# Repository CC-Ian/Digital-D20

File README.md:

# Big Electronic D20

This project began several years ago, before pixel dice became widely available. Inspired by existing designs but aiming for something unique, this marks my first foray into PCB art. By adding artwork to the solder mask layer, the FR4 substrate is exposed, allowing light to shine through. Combined with a 3D-printed frame, a mainboard featuring LEDs, and an IMU, the result is a visually striking D20 that comes to life when rolled.

## Showcase

## Faces

- Each face is an equilateral triangle, 1.5" per edge.
- Single-sided PCBs with gold-plated numbers.
- Solder mask is relieved around each number for clear illumination.
- Lightning patterns are masked out for added visual interest.
- Designs were refined following prototype testing with various patterns.

## Frame

- Constructed from MJF-printed nylon in an icosahedral shape.
- Features inset shelves for gluing PCB faces.
- Includes cut-outs along two opposing spokes to accommodate the rectangular mainboard.

## Mainboard

- STM32L412KB microcontroller.
- LIS2DW12 MEMS IMU.
- 32 addressable LEDs.
- Voltage regulators and LiPo battery charging circuitry.
- Ultra-low power design: enters deep sleep mode when not in use.

### Operation

- The IMU detects motion, waking the microcontroller.
- LEDs activate and display a lightning animation while the die is in motion.
- The IMU is regularly polled during animation.
- When the die comes to rest, a final measurement determines the top face using cosine similarity.
- The face value determines the display color: pure red for 1, pure green for 20, with a linear gradient for intermediate values.
- The color is shown for a few seconds before returning to sleep mode.

### Power Consumption

- At rest: ~5μA, yielding a theoretical shelf life of ~5 years with a 400mAh battery.
- During operation: ~50mA, for a theoretical runtime of ~10 hours.
- Designed for intermittent use, suitable for multiple gaming sessions per charge.

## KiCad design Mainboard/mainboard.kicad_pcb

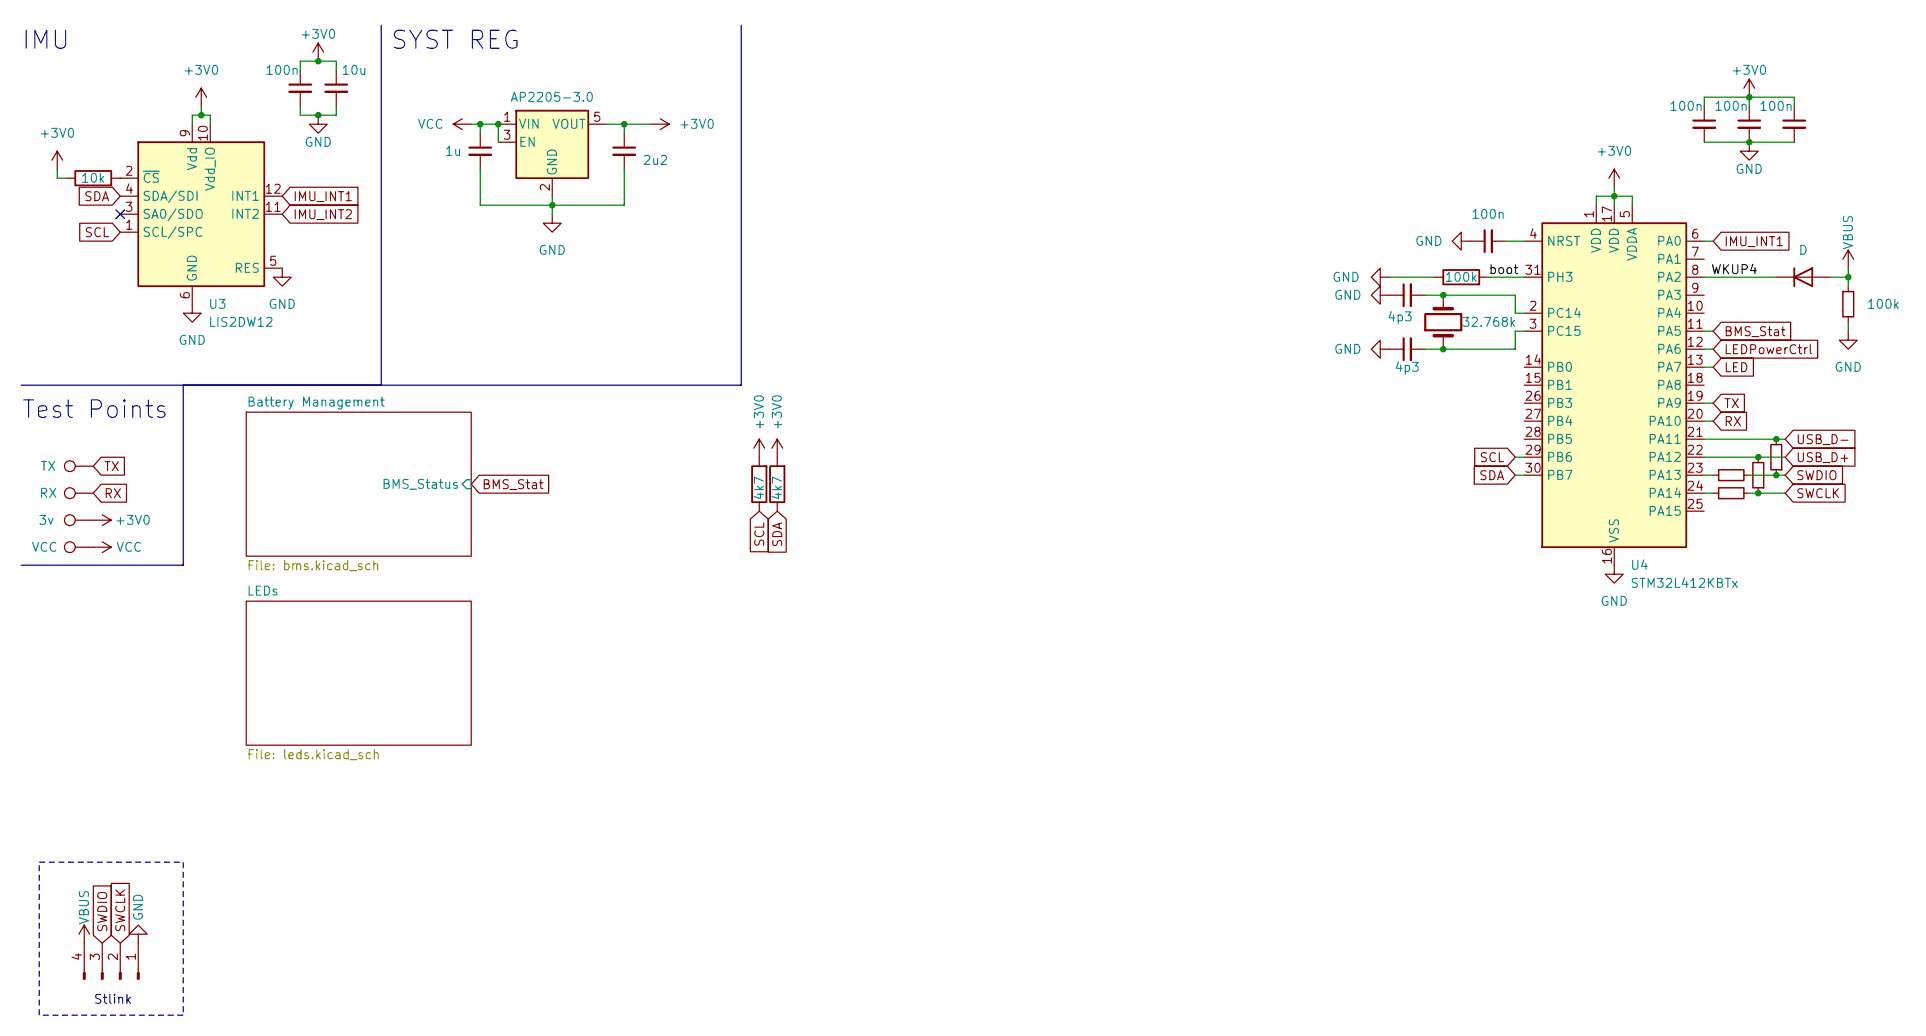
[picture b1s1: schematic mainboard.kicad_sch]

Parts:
3v0: 3v; TestPoint_Pad_D1.0mm
C3, C5, C6, C7, C10: 100n; C_0402_1005Metric
C4: 10u; C_0402_1005Metric
C8: 1u; C_0402_1005Metric
C9: 2u2; C_0402_1005Metric
C12, C13: 4p3; C_0402_1005Metric
D33: D; D_SOD-323
J1: Conn_01x04_Pin; PinHeader_1x04_P2.54mm_Vertical
R2: 10k; R_0402_1005Metric
R3, R12: R_Small; R_0201_0603Metric
R4, R10: 100k; R_0402_1005Metric
R6, R7: 4k7; R_0402_1005Metric
R13, R14: R_Small; R_0402_1005Metric
RX1: RX; TestPoint_Pad_D1.0mm
TP9: VCC; TestPoint_Pad_D1.0mm
TX1: TX; TestPoint_Pad_D1.0mm
U1: AP2205-3.0; SOT-23-5
U3: LIS2DW12; LGA-12_2x2mm_P0.5mm
U4: STM32L412KBTx; LQFP-32_7x7mm_P0.8mm
Y1: 32.768k; Crystal_SMD_3215-2Pin_3.2x1.5mm

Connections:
+3V0: 3v0.1, C3.1, C4.1, C5.1, C6.1, C7.1, C9.1, R2.1, R6.2, R7.2, U1.5 (VOUT), U3.9 (Vdd), U3.10 (Vdd_IO), U4.1 (VDD), U4.5 (VDDA), U4.17 (VDD)
/WKUP4: D33.1 (K), U4.8 (PA2)
/boot: R4.2, U4.31 (PH3)
BMS_Stat: U4.11 (PA5); also elsewhere on the board
GND: C3.2, C4.2, C5.2, C6.2, C7.2, C8.2, C9.2, C10.1, C12.1, C13.1, J1.1, R4.1, R10.2, U1.2 (GND), U3.5 (RES), U3.6 (GND), U3.7 (GND), U3.8 (GND), U4.16 (VSS), U4.32 (VSS); also elsewhere on the board
IMU_INT1: U3.12 (INT1), U4.6 (PA0)
IMU_INT2: U3.11 (INT2)
LED: U4.13 (PA7); also elsewhere on the board
LEDPowerCtrl: U4.12 (PA6); also elsewhere on the board
unnamed: R2.2, U3.2 (~CS)
unnamed: C10.2, U4.4 (NRST)
unnamed: R3.1, U4.23 (PA13)
unnamed: R12.1, U4.24 (PA14)
unnamed: C12.2, U4.2 (PC14), Y1.2
unnamed: C13.2, U4.3 (PC15), Y1.1
RX: RX1.1, U4.20 (PA10)
SCL: R6.1, U3.1 (SCL/SPC), U4.29 (PB6)
SDA: R7.1, U3.4 (SDA/SDI), U4.30 (PB7)
SWCLK: J1.2, R12.2, R13.1
SWDIO: J1.3, R3.2, R14.1
TX: TX1.1, U4.19 (PA9)
USB_D+: R13.2, U4.22 (PA12)
USB_D-: R14.2, U4.21 (PA11)
VBUS: D33.2 (A), J1.4, R10.1; also elsewhere on the board
VCC: C8.1, TP9.1, U1.1 (VIN), U1.3 (EN); also elsewhere on the board

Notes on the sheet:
Test Points
SYST REG
Stlink
IMU

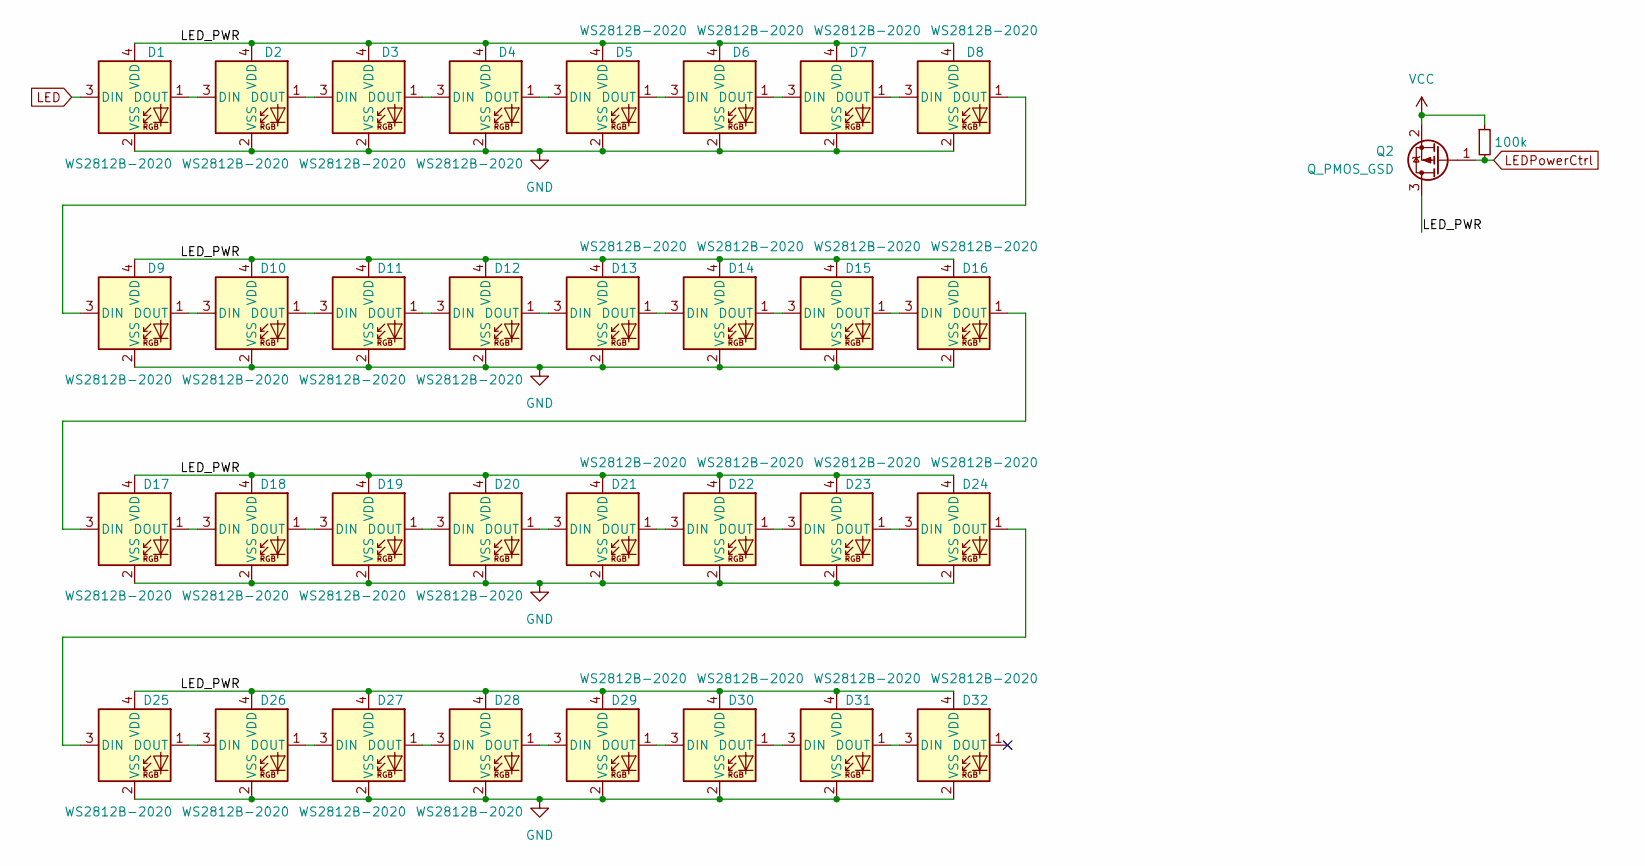
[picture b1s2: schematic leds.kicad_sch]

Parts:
D1, D2, D3, D4, D5, D6, D7, D8, D9, D10, D11, D12, D13, D14, D15, D16, D17, D18, D19, D20, D21, D22, D23, D24, D25, D26, D27, D28, D29, D30, D31, D32: WS2812B-2020; LED_WS2812B-2020_PLCC4_2.0x2.0mm
Q2: Q_PMOS_GSD; SOT-23
R9: 100k; R_0402_1005Metric

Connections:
/LEDs/LED_PWR: D1.4 (VDD), D2.4 (VDD), D3.4 (VDD), D4.4 (VDD), D5.4 (VDD), D6.4 (VDD), D7.4 (VDD), D8.4 (VDD), D9.4 (VDD), D10.4 (VDD), D11.4 (VDD), D12.4 (VDD), D13.4 (VDD), D14.4 (VDD), D15.4 (VDD), D16.4 (VDD), D17.4 (VDD), D18.4 (VDD), D19.4 (VDD), D20.4 (VDD), D21.4 (VDD), D22.4 (VDD), D23.4 (VDD), D24.4 (VDD), D25.4 (VDD), D26.4 (VDD), D27.4 (VDD), D28.4 (VDD), D29.4 (VDD), D30.4 (VDD), D31.4 (VDD), D32.4 (VDD), Q2.3 (D)
GND: D1.2 (VSS), D2.2 (VSS), D3.2 (VSS), D4.2 (VSS), D5.2 (VSS), D6.2 (VSS), D7.2 (VSS), D8.2 (VSS), D9.2 (VSS), D10.2 (VSS), D11.2 (VSS), D12.2 (VSS), D13.2 (VSS), D14.2 (VSS), D15.2 (VSS), D16.2 (VSS), D17.2 (VSS), D18.2 (VSS), D19.2 (VSS), D20.2 (VSS), D21.2 (VSS), D22.2 (VSS), D23.2 (VSS), D24.2 (VSS), D25.2 (VSS), D26.2 (VSS), D27.2 (VSS), D28.2 (VSS), D29.2 (VSS), D30.2 (VSS), D31.2 (VSS), D32.2 (VSS); also elsewhere on the board
LED: D1.3 (DIN); also elsewhere on the board
LEDPowerCtrl: Q2.1 (G), R9.2; also elsewhere on the board
unnamed: D1.1 (DOUT), D2.3 (DIN)
unnamed: D2.1 (DOUT), D3.3 (DIN)
unnamed: D3.1 (DOUT), D4.3 (DIN)
unnamed: D4.1 (DOUT), D5.3 (DIN)
unnamed: D5.1 (DOUT), D6.3 (DIN)
unnamed: D6.1 (DOUT), D7.3 (DIN)
unnamed: D7.1 (DOUT), D8.3 (DIN)
unnamed: D8.1 (DOUT), D9.3 (DIN)
unnamed: D9.1 (DOUT), D10.3 (DIN)
unnamed: D10.1 (DOUT), D11.3 (DIN)
unnamed: D11.1 (DOUT), D12.3 (DIN)
unnamed: D12.1 (DOUT), D13.3 (DIN)
unnamed: D13.1 (DOUT), D14.3 (DIN)
unnamed: D14.1 (DOUT), D15.3 (DIN)
unnamed: D15.1 (DOUT), D16.3 (DIN)
unnamed: D16.1 (DOUT), D17.3 (DIN)
unnamed: D17.1 (DOUT), D18.3 (DIN)
unnamed: D18.1 (DOUT), D19.3 (DIN)
unnamed: D19.1 (DOUT), D20.3 (DIN)
unnamed: D20.1 (DOUT), D21.3 (DIN)
unnamed: D21.1 (DOUT), D22.3 (DIN)
unnamed: D22.1 (DOUT), D23.3 (DIN)
unnamed: D23.1 (DOUT), D24.3 (DIN)
unnamed: D24.1 (DOUT), D25.3 (DIN)
unnamed: D25.1 (DOUT), D26.3 (DIN)
unnamed: D26.1 (DOUT), D27.3 (DIN)
unnamed: D27.1 (DOUT), D28.3 (DIN)
unnamed: D28.1 (DOUT), D29.3 (DIN)
unnamed: D29.1 (DOUT), D30.3 (DIN)
unnamed: D30.1 (DOUT), D31.3 (DIN)
unnamed: D31.1 (DOUT), D32.3 (DIN)
VCC: Q2.2 (S), R9.1; also elsewhere on the board

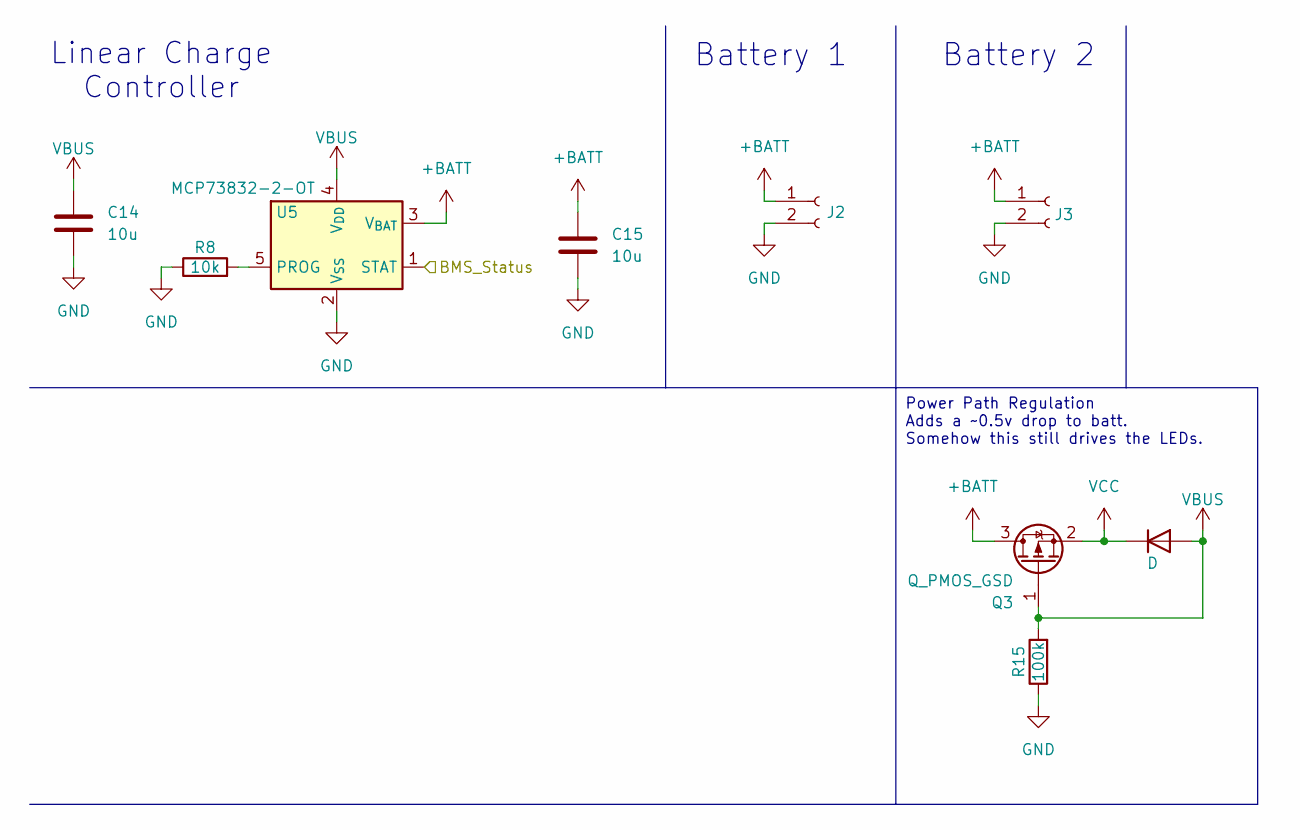
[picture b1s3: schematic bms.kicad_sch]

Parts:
C14, C15: 10u; C_0603_1608Metric
D34: D; D_SOD-323
J2, J3: Conn_01x02_Socket; PinHeader_1x02_P2.00mm_Vertical
Q3: Q_PMOS_GSD; SOT-23
R8: 10k; R_0402_1005Metric
R15: 100k; R_0402_1005Metric
U5: MCP73832-2-OT; SOT-23-5

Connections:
+BATT: C15.1, J2.1, J3.1, Q3.3 (D), U5.3 (V_{BAT})
BMS_Stat: U5.1 (STAT); also elsewhere on the board
GND: C14.2, C15.2, J2.2, J3.2, R8.1, R15.1, U5.2 (V_{SS}); also elsewhere on the board
unnamed: R8.2, U5.5 (PROG)
VBUS: C14.1, D34.2 (A), Q3.1 (G), R15.2, U5.4 (V_{DD}); also elsewhere on the board
VCC: D34.1 (K), Q3.2 (S); also elsewhere on the board

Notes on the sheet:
Battery 1
Battery 2
Linear Charge Controller
Power Path Regulation Adds a ~0.5v drop to batt. Somehow this still drives the LEDs.

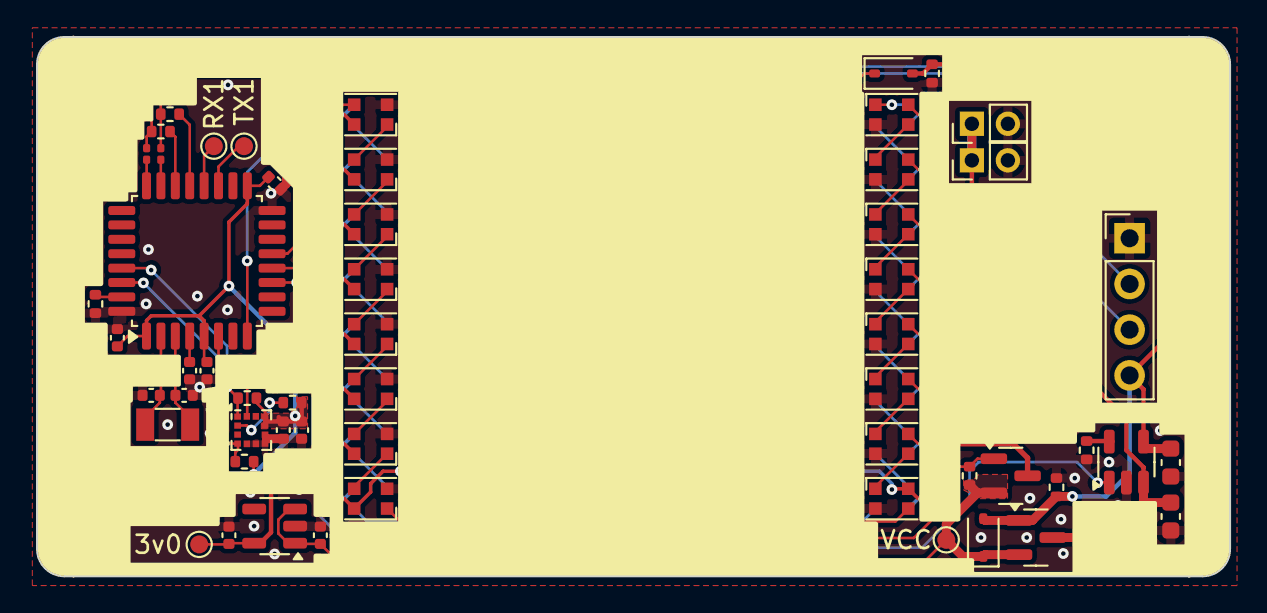
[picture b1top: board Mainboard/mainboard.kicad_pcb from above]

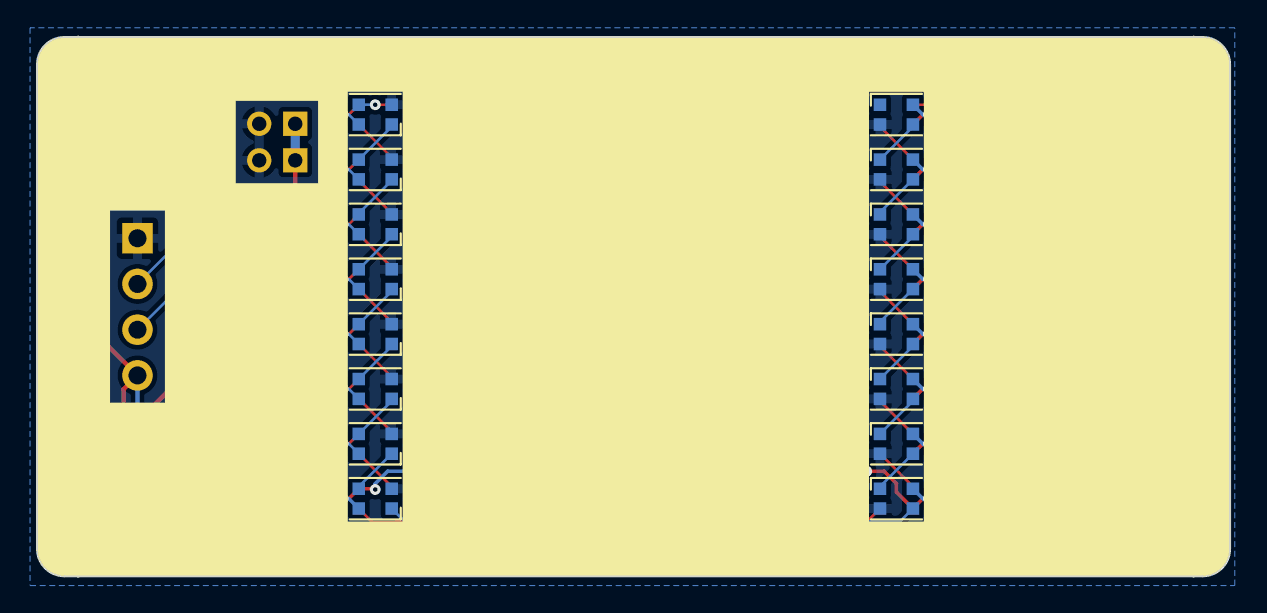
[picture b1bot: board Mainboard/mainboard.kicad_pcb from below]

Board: 2 copper layers, 66.3 x 30.0 mm, 72 parts (16 on the bottom side), 58 nets.

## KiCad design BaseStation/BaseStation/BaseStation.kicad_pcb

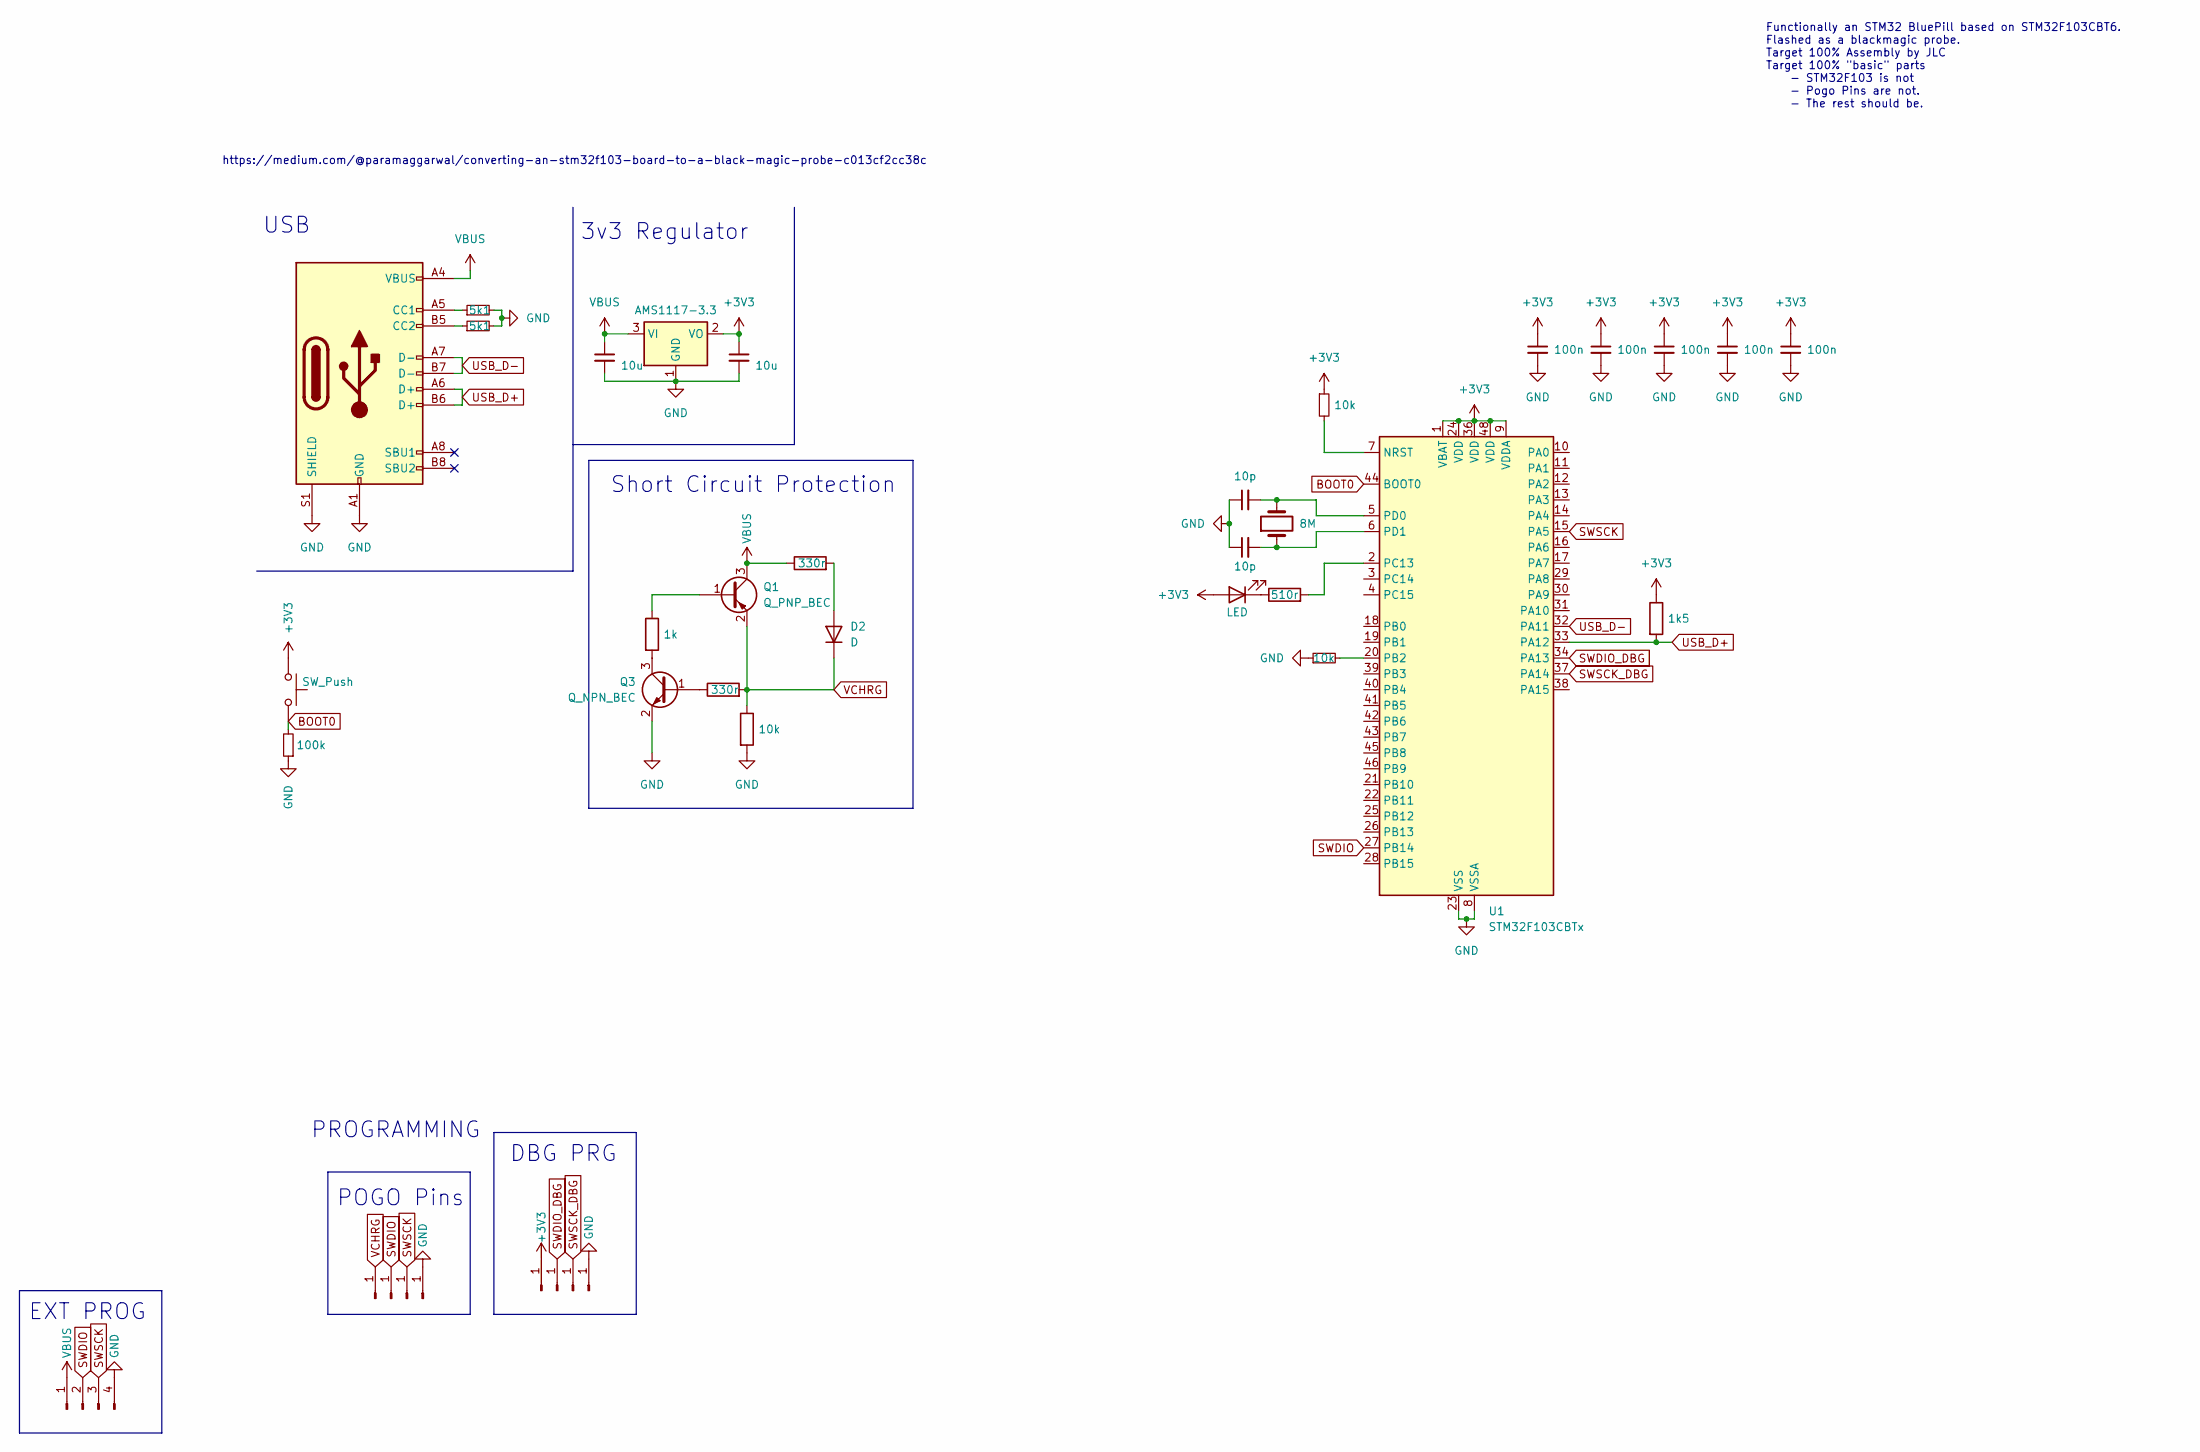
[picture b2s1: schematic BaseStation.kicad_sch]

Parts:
C1, C2: 10u; C_0603_1608Metric
C3, C4: 10p; C_0402_1005Metric
C5, C6, C7, C8, C9: 100n; C_0402_1005Metric
D1: LED; LED_0603_1608Metric
D2: D; D_SOD-323
J1: USB_C_Receptacle_USB2.0_16P; USB_C_Receptacle_HRO_TYPE-C-31-M-12
J2, J3, J4, J5: Conn_01x01_Pin; TestPoint_Loop_D3.50mm_Drill0.9mm_Beaded
J6, J7, J8, J9: Conn_01x01_Pin; TestPoint_Pad_D1.5mm
J10: Conn_01x04_Pin; PinHeader_1x04_P2.54mm_Horizontal
Q1: Q_PNP_BEC; SOT-23
Q3: Q_NPN_BEC; SOT-23
R1, R2: 5k1; R_0603_1608Metric
R3, R4: 10k; R_0603_1608Metric
R5: 100k; R_0603_1608Metric
R6: 510r; R_0603_1608Metric
R7: 1k; R_0402_1005Metric
R8, R10: 330r; R_0402_1005Metric
R9: 10k; R_0402_1005Metric
R11: 1k5; R_0402_1005Metric
SW1: SW_Push; SW_SPST_SKQG_WithStem
U1: STM32F103CBTx; LQFP-48_7x7mm_P0.5mm
U2: AMS1117-3.3; SOT-223-3_TabPin2
Y2: 8M; Crystal_SMD_5032-2Pin_5.0x3.2mm; Part X50328MSB2GI

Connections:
+3V3: C2.1, C5.1, C6.1, C7.1, C8.1, C9.1, D1.2 (A), J6.1, R3.1, R11.1, SW1.1, U1.1 (VBAT), U1.9 (VDDA), U1.24 (VDD), U1.36 (VDD), U1.48 (VDD), U2.2 (VO)
BOOT0: R5.2, SW1.2, U1.44 (BOOT0)
GND: C1.2, C2.2, C3.1, C4.1, C5.2, C6.2, C7.2, C8.2, C9.2, J1.A1 (GND), J1.A12 (GND), J1.B1 (GND), J1.B12 (GND), J1.S1 (SHIELD), J5.1, J9.1, J10.4, Q3.2 (E), R1.2, R2.2, R4.1, R5.1, R9.2, U1.8 (VSSA), U1.23 (VSS), U1.35 (VSS), U1.47 (VSS), U2.1 (GND)
unnamed: D1.1 (K), R6.1
unnamed: D2.2 (A), R10.2
unnamed: J1.A5 (CC1), R1.1
unnamed: J1.B5 (CC2), R2.1
unnamed: Q1.1 (B), R7.1
unnamed: Q3.1 (B), R8.1
unnamed: Q3.3 (C), R7.2
unnamed: R3.2, U1.7 (NRST)
unnamed: R4.2, U1.20 (PB2)
unnamed: R6.2, U1.2 (PC13)
unnamed: C3.2, U1.5 (PD0), Y2.2
unnamed: C4.2, U1.6 (PD1), Y2.1
SWDIO: J3.1, J10.2, U1.27 (PB14), U1.28 (PB15)
SWDIO_DBG: J7.1, U1.34 (PA13)
SWSCK: J4.1, J10.3, U1.15 (PA5)
SWSCK_DBG: J8.1, U1.37 (PA14)
USB_D+: J1.A6 (D+), J1.B6 (D+), R11.2, U1.33 (PA12)
USB_D-: J1.A7 (D-), J1.B7 (D-), U1.32 (PA11)
VBUS: C1.1, J1.A4 (VBUS), J1.A9 (VBUS), J1.B4 (VBUS), J1.B9 (VBUS), J10.1, Q1.3 (C), R10.1, U2.3 (VI)
VCHRG: D2.1 (K), J2.1, Q1.2 (E), R8.2, R9.1

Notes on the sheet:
DBG PRG
3v3 Regulator
Short Circuit Protection
USB
https://medium.com/@paramaggarwal/converting-an-stm32f103-board-to-a-black-magic-probe-c013cf2cc38c
PROGRAMMING
EXT PROG
Functionally an STM32 BluePill based on STM32F103CBT6. Flashed as a blackmagic probe. Target 100% Assembly by JLC Target 100% "basic" parts - STM32F103 is not - Pogo Pins are not. - The rest should be.
POGO Pins

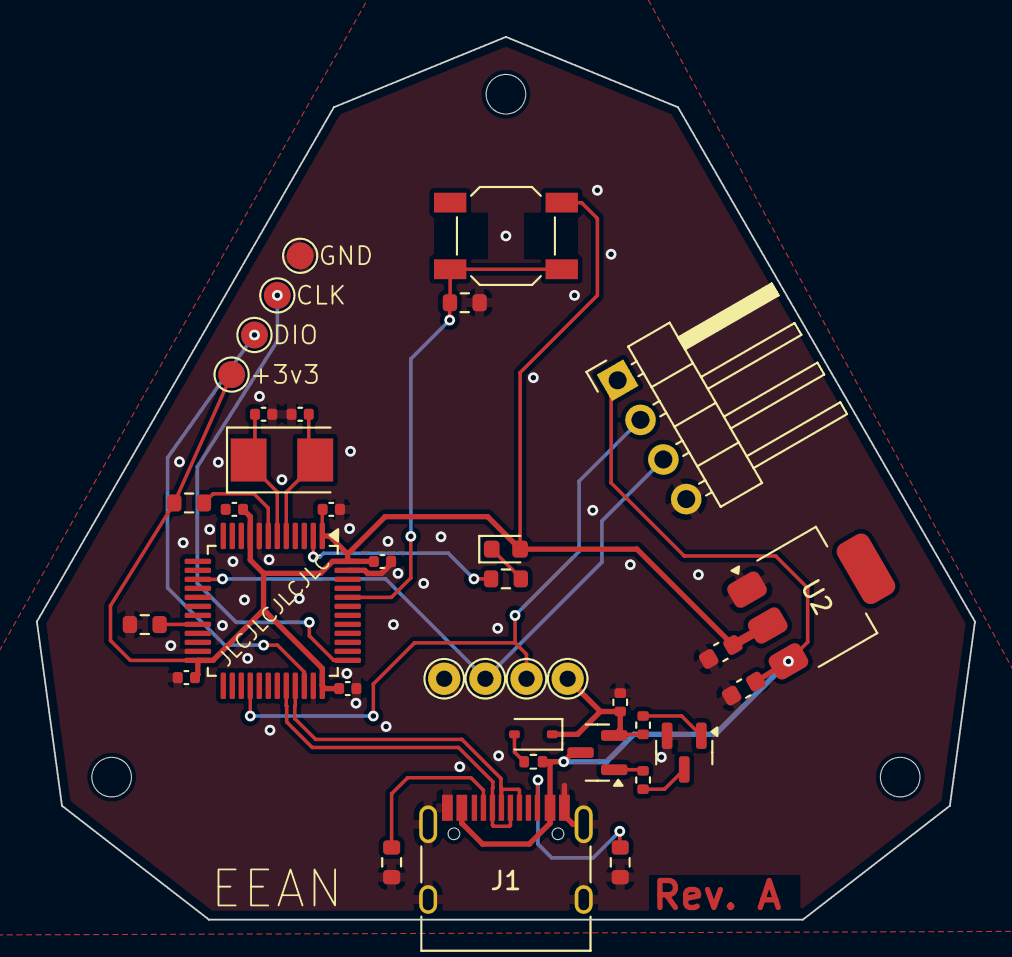
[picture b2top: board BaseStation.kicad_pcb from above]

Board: 2 copper layers, 52.1 x 49.0 mm, 37 parts (0 on the bottom side), 23 nets.

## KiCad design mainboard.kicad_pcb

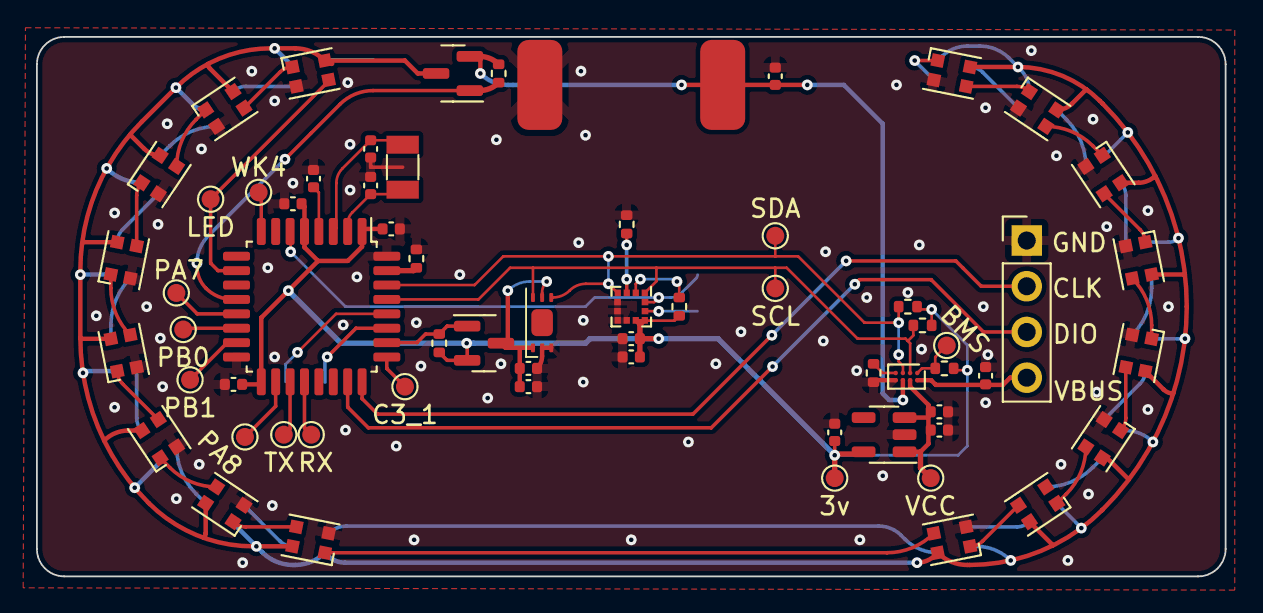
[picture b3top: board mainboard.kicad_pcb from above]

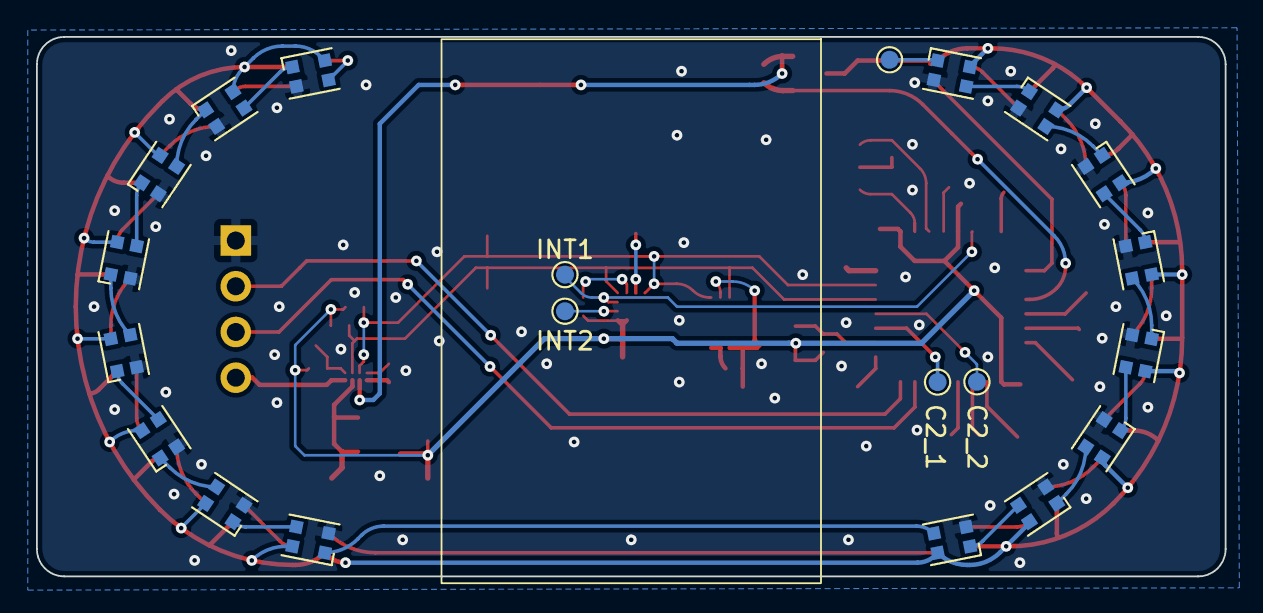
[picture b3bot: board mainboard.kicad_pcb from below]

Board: 2 copper layers, 66.0 x 30.0 mm, 52 parts (4 on the bottom side), 33 nets.

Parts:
BT1: 200mAh; battery_20x30
C1, C4: 10u; C_0402_1005Metric
C2, C8, C11: 1u; C_0402_1005Metric
C3, C5, C6, C7, C10, C14, C15: 100n; C_0402_1005Metric
C9: 2u2; C_0402_1005Metric
C12, C13: 4p3; C_0402_1005Metric
J1: Conn_01x04_Pin; PinHeader_1x04_P2.54mm_Vertical
Q1, Q2: Q_PMOS_GSD; SOT-23
R1, R2, R4, R5: 10k; R_0402_1005Metric
R3: 0; R_0402_1005Metric
R6, R7: 4k7; R_0402_1005Metric
R8, R9: 100k; R_0402_1005Metric
RX1: RX; TestPoint_Pad_D1.0mm
TP1: PB0; TestPoint_Pad_D1.0mm
TP2: PA7; TestPoint_Pad_D1.0mm
TP3: PB1; TestPoint_Pad_D1.0mm
TP4: PA8; TestPoint_Pad_D1.0mm
TP5: SDA; TestPoint_Pad_D1.0mm
TP6: SCL; TestPoint_Pad_D1.0mm
TP7: INT1; TestPoint_Pad_D1.0mm
TP8: INT2; TestPoint_Pad_D1.0mm
TP9: VCC; TestPoint_Pad_D1.0mm
TP10: 3v; TestPoint_Pad_D1.0mm
TP11: BMS; TestPoint_Pad_D1.0mm
TP12: LED; TestPoint_Pad_D1.0mm
TP13: WK4; TestPoint_Pad_D1.0mm
TP14: C2_1; TestPoint_Pad_D1.0mm
TP15: C2_2; TestPoint_Pad_D1.0mm
TP16: C3_1; TestPoint_Pad_D1.0mm
TP17: TX; TestPoint_Pad_D1.0mm
U1: AP2205-3.0; SOT-23-5
U2: BQ21080; Texas_DSBGA-8-1.04x1.59mm
U3: LIS2DW12; LGA-12_2x2mm_P0.5mm
U4: STM32L412KBTx; LQFP-32_7x7mm_P0.8mm
U5: BH1730; WSOF6
Y1: 32.768k; Crystal_SMD_3215-2Pin_3.2x1.5mm

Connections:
+3V0: C3.1, C4.1, C5.1, C6.1, C7.1, C9.1, Q1.2 (S), R1.2, R2.1, R6.2, R7.2, R8.1, TP10.1, U1.5 (VOUT), U3.9 (Vdd), U3.10 (Vdd_IO), U4.1 (VDD), U4.5 (VDDA), U4.17 (VDD)
+BATT: BT1.1 (+), C11.1, Q2.2 (S), R9.1, U2.C2 (BAT)
ALVCC: C14.1, C15.1, Q1.3 (D), U5.1 (VCC), U5.5 (DVI)
BH1730PowerCtrl: Q1.1 (G), R8.2, U4.26 (PB3)
GND: BT1.2 (-), C1.2, C2.2, C3.2, C4.2, C5.2, C6.2, C7.2, C8.2, C9.2, C10.1, C11.2, C12.1, C13.1, C14.2, C15.2, J1.1, R3.1, R4.1, R5.1, U1.2 (GND), U2.D2 (GND), U3.5 (RES), U3.6 (GND), U3.7 (GND), U3.8 (GND), U4.16 (VSS), U4.32 (VSS), U5.2 (INT), U5.3 (GND)
IMU_INT1: TP7.1, U3.12 (INT1), U4.6 (PA0)
IMU_INT2: TP8.1, U3.11 (INT2)
LED IN: TP12.1, U4.10 (PA4)
LEDPowerCtrl: Q2.1 (G), R9.2, U4.12 (PA6)
unnamed: R3.2, U3.3 (SA0/SDO)
unnamed: R2.2, U3.2 (~CS)
unnamed: C10.2, U4.4 (NRST)
unnamed: TP2.1, U4.13 (PA7)
unnamed: TP4.1, U4.18 (PA8)
unnamed: TP1.1, U4.14 (PB0)
unnamed: TP3.1, U4.15 (PB1)
unnamed: C12.2, U4.2 (PC14), Y1.2
unnamed: C13.2, U4.3 (PC15), Y1.1
unnamed: R4.2, U4.31 (PH3)
RX: RX1.1, U4.20 (PA10)
SCL: R6.1, TP6.1, U2.B1 (SCL), U3.1 (SCL/SPC), U4.29 (PB6), U5.6 (SCL)
SDA: R7.1, TP5.1, U2.C1 (SDA), U3.4 (SDA/SDI), U4.30 (PB7), U5.4 (SDA)
SWCLK: J1.2, U4.24 (PA14)
SWDIO: J1.3, U4.23 (PA13)
TSC_G2_IO1: TP14.1, U4.27 (PB4)
TSC_G2_IO2: TP15.1, U4.28 (PB5)
TSC_G3_IO1: TP16.1, U4.25 (PA15)
TS|MR: R5.2, U2.D1 (TS|MR)
TX: TP17.1, U4.19 (PA9)
VBUS: C2.1, J1.4, U2.A2 (IN)
VCC: C1.1, C8.1, TP9.1, U1.1 (VIN), U1.3 (EN), U2.B2 (SYS)
WKUP4: TP13.1, U4.8 (PA2)
~BMS_INT: R1.1, TP11.1, U2.A1 (~INT)

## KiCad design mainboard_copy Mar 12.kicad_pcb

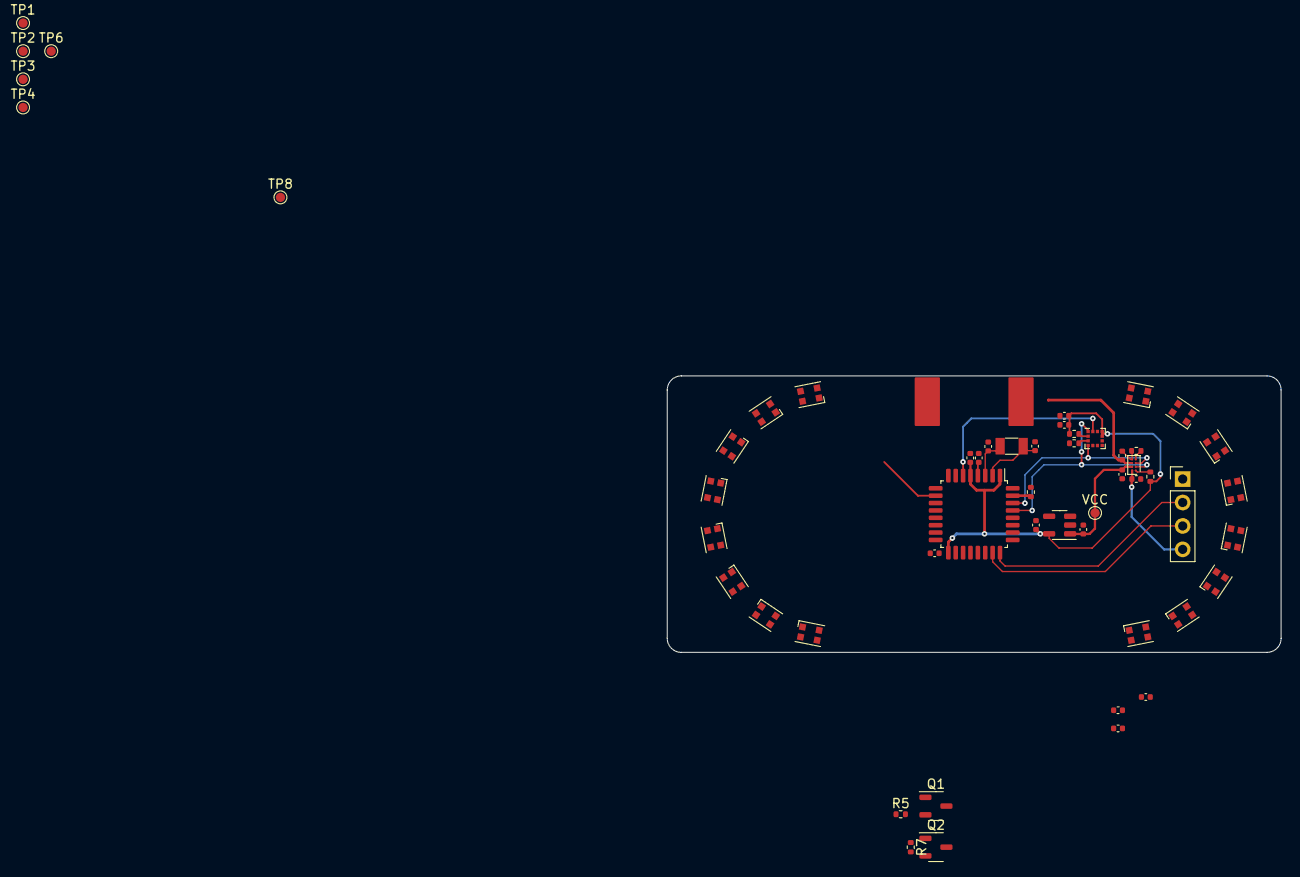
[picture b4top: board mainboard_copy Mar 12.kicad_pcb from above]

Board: 2 copper layers, 66.5 x 30.0 mm, 37 parts (0 on the bottom side), 21 nets.

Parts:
C1: 2u2; C_0402_1005Metric
C2, C5, C6: 1u; C_0402_1005Metric
C3, C7: 10u; C_0402_1005Metric
C4, C8, C9, C10, C13, C14, C15: 100n; C_0402_1005Metric
C11, C12: 4p3; C_0402_1005Metric
J1: Conn_01x04_Pin; PinHeader_1x04_P2.54mm_Vertical
Q1, Q2: PMOS; SOT-23-3
R1, R3, R4, R6: 10k; R_0402_1005Metric
R2: 0; R_0402_1005Metric
R5, R7: 100k; R_0402_1005Metric
TP1: SDA; TestPoint_Pad_D1.0mm
TP2: SCL; TestPoint_Pad_D1.0mm
TP3: INT1; TestPoint_Pad_D1.0mm
TP4: INT2; TestPoint_Pad_D1.0mm
TP6: 3v; TestPoint_Pad_D1.0mm
TP8: GND; TestPoint_Pad_D1.0mm
U1: LIS2DW12; LGA-12_2x2mm_P0.5mm
U2: AP2205-3.0; SOT-23-5
U3: BQ21080; Texas_DSBGA-8-1.04x1.59mm
U4: STM32L412KBTx; LQFP-32_7x7mm_P0.8mm
VCC: VCC; TestPoint_Pad_D1.0mm
Y1: 32.768k; Crystal_SMD_3215-2Pin_3.2x1.5mm

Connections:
+3V0: C1.1, C3.1, C4.1, C8.1, C9.1, C13.1, C14.1, C15.1, Q1.3 (S), Q2.3 (S), R1.1, R4.2, R5.1, R7.1, TP6.1, U1.9 (Vdd), U1.10 (Vdd_IO), U2.5 (VOUT), U4.1 (VDD), U4.5 (VDDA), U4.17 (VDD)
+BATT: C5.1, U3.C2 (BAT)
BH1730PowerCtrl: Q1.2 (G), R5.2, U4.13 (PA7)
GND: C1.2, C2.2, C3.2, C4.2, C5.2, C6.2, C7.2, C8.2, C9.2, C10.1, C11.1, C12.1, C13.2, C14.2, C15.2, J1.1, R2.1, R3.1, R6.1, TP8.1, U1.5 (RES), U1.6 (GND), U1.7 (GND), U1.8 (GND), U2.2 (GND), U2.3 (EN), U3.D2 (GND), U4.16 (VSS), U4.32 (VSS)
IMU_INT1: TP3.1, U1.12 (INT1), U4.6 (PA0)
IMU_INT2: TP4.1, U1.11 (INT2)
LEDP0werCtrl: Q2.2 (G), R7.2
unnamed: R2.2, U1.3 (SA0/SDO)
unnamed: R1.2, U1.2 (~CS)
unnamed: C10.2, U4.4 (NRST)
unnamed: C11.2, U4.2 (PC14), Y1.2
unnamed: C12.2, U4.3 (PC15), Y1.1
unnamed: R6.2, U4.31 (PH3)
SCL: TP2.1, U1.1 (SCL/SPC), U3.B1 (SCL), U4.29 (PB6)
SDA: TP1.1, U1.4 (SDA/SDI), U3.C1 (SDA), U4.30 (PB7)
SWCLK: J1.2, U4.24 (PA14)
SWDIO: J1.3, U4.23 (PA13)
TS|MR: R3.2, U3.D1 (TS|MR)
VBUS: C6.1, J1.4, U3.A2 (IN)
VCC: C2.1, C7.1, U2.1 (VIN), U3.B2 (SYS), VCC.1
~BMS_INT: R4.1, U3.A1 (~INT)

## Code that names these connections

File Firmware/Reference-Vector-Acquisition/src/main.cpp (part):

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// BQ21080 BMS Registers
#define BMS_ADDRESS 0x6A
#define BMS_REG_ICHG_CTRL 0x04
#define BMS_STAT_PIN PA5

// Neopixel configs
#define NUM_LEDS 32
#define LED_DATA_PIN PA7
#define LED_BRIGHTNESS 200
#define LED_ENABLE PA6


// IMU Structure
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void SystemClock_Config(void);
void SystemPower_Config(void);

/// @brief Enable WKUP 1 and WKUP4 pins on a rising edge.
void configureWakeupPins(bool shake = true, bool charge = true) {
  // GPIO 1 (WKUP1) [PA0]
  GPIO_InitTypeDef GPIO_InitStruct = {0};
  __HAL_RCC_GPIOA_CLK_ENABLE();
  GPIO_InitStruct.Pin = GPIO_PIN_1;
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  GPIO_InitStruct.Pull = GPIO_PULLDOWN;
  HAL_GPIO_Init(GPIOA, &GPIO_InitStruct);

  // GPIO 3 (WKUP4) [PA2]
  GPIO_InitStruct.Pin = GPIO_PIN_3;
  GPIO_InitStruct.Mode = GPIO_MODE_INPUT;
  GPIO_InitStruct.Pull = GPIO_PULLDOWN;
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  /* Clear all related wakeup flags */
  __HAL_PWR_CLEAR_FLAG(PWR_FLAG_WU);
    
  /* Enable wakeup pins WKUP1 and WKUP4 */
  if (shake) {
    HAL_PWR_EnableWakeUpPin(PWR_WAKEUP_PIN1_HIGH);
  }
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  digitalWrite(LED_ENABLE, HIGH);

  // WAKEUP4. Connected to Vin.
  pinMode(PA2, INPUT_PULLDOWN);
  

  // Slight delay in startup for settle and timing.
  HAL_Delay(100);

  // Initialize IMU in wake mode. Higher current draw, for more readings per second.
  Wire.setSCL(PB6); // Set Clock pin.
  Wire.setSDA(PB7); // Set Data Pin.
  Wire.begin();

  initIMU();
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
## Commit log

2024-02-06 Initial test board. 6L to abuse jlc
2024-02-06 Add 'jlcjlcjlcjlc' to mark order number placement.
2024-03-07 The test board I ordered
2024-03-07 Clear out old files
2024-03-07 Begin layout. IMU, BMS, Sys_REG all complete. Working MCU.
2024-03-10 Diode layout, majority of schema, tile thoughts
2024-03-10 add svgs
2024-03-11 Tiles rev 1. would like to tweak the lightning bolts, and doonce again try to get a nice back copper pour. Might not happen.
2024-03-11 Tiles rev 1 with test gerbers.
2024-03-13 Rev A layout. pending review
2024-03-16 Rev 0 layout complete. ORdering as protoptype.
2024-03-18 First roughly working firmware
2024-04-03 switch to 4 groups of boards?
2024-04-03 re-org project. This is how it should've been from the start.
2024-04-06 Updates to firmware. Suspect bad mean/stdev calculations
2024-04-06 Actually write the register I want to write into.
2024-04-06 Functional Code. Global number of readings. TDO: Proper math to compute the length of the array.
2024-04-06 Use All 32 LEDs, better stdev and mean math which doesn't hit a global.
2024-04-06 Something to do with the i2c device test
2024-04-07 Pull in faces. Begin modifying schema.
2024-04-09 Increase LED Brightness, Add free fall and impact guarding to main calculation loop.
2024-04-10 Re-tool faces. It costs nothing to add the extra panelization holes. They bill this as 20 designs regardless.
2024-04-10 Begin the base station layout (BMP)
2025-01-15 Somewhere around the first complete prototype. time to change BMS
2025-02-07 New Hardware; LED data moved from PA4 to PA7
2025-02-07 New hardware; attempt to correct BMS failures, better layout and routing, bom only change to allow swap to USB DFU Bootloader/upload
2025-07-16 V2 mainboard, some firmware stuffs, free design files I guess
2025-07-16 add readme and images
